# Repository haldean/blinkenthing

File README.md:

blinkenthing
============

turning a black bike into a rainbow monstrosity

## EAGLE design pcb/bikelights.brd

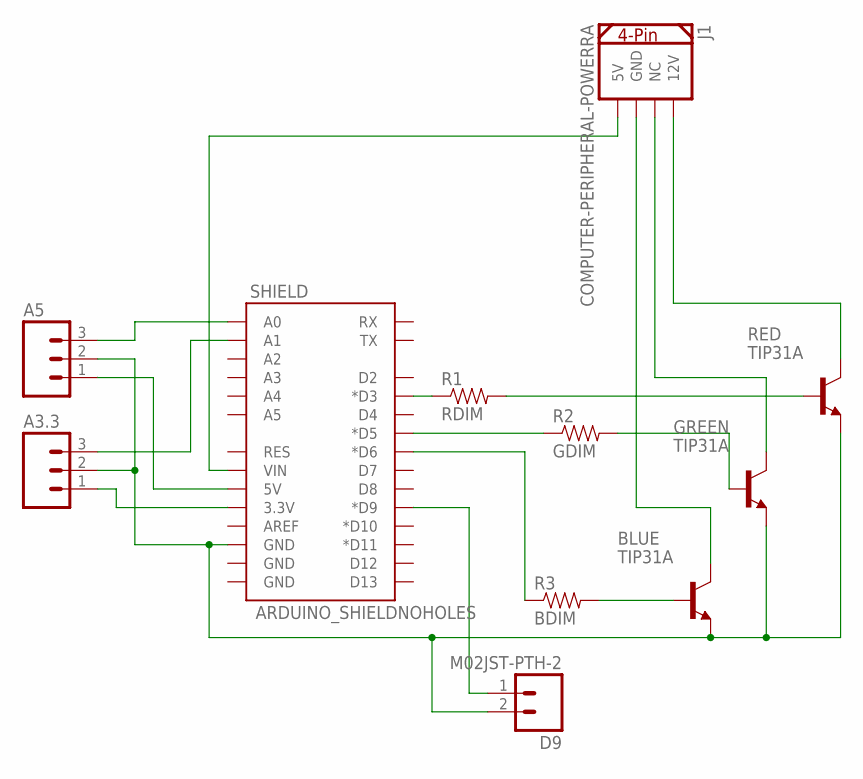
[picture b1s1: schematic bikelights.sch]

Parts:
A3.3, A5: M03JST-PTH; JST-3-PTH
BLUE: TIP31A; TO220
D9: M02JST-PTH-2; JST-2-PTH
GREEN: TIP31A; TO220
J1: COMPUTER-PERIPHERAL-POWERRA; COMPUTER-PERIPHERAL-POWER-RA
R1: RDIM; AXIAL-0.3EZ
R2: GDIM; AXIAL-0.3EZ
R3: BDIM; AXIAL-0.3EZ
RED: TIP31A; TO220
SHIELD: ARDUINO_SHIELDNOHOLES; DUEMILANOVE_SHIELD_NOHOLES

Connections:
unnamed: R1.P$1 (1), SHIELD.D3 (*D3)
unnamed: GREEN.1 (B), R2.P$2 (2)
unnamed: BLUE.1 (B), R3.P$2 (2)
unnamed: A3.3.2, A5.2, BLUE.3 (E), D9.2, GREEN.3 (E), RED.3 (E), SHIELD.GND@2 (GND)
unnamed: BLUE.2 (C), J1.GND
unnamed: GREEN.2 (C), J1.NC
unnamed: J1.12V, RED.2 (C)
unnamed: J1.5V, SHIELD.VIN
unnamed: R2.P$1 (1), SHIELD.D5 (*D5)
unnamed: R3.P$1 (1), SHIELD.D6 (*D6)
unnamed: R1.P$2 (2), RED.1 (B)
unnamed: A5.1, SHIELD.5V
unnamed: D9.1, SHIELD.D9 (*D9)
unnamed: A5.3, SHIELD.A0
unnamed: A3.3.3, SHIELD.A1
unnamed: A3.3.1, SHIELD.3.3V

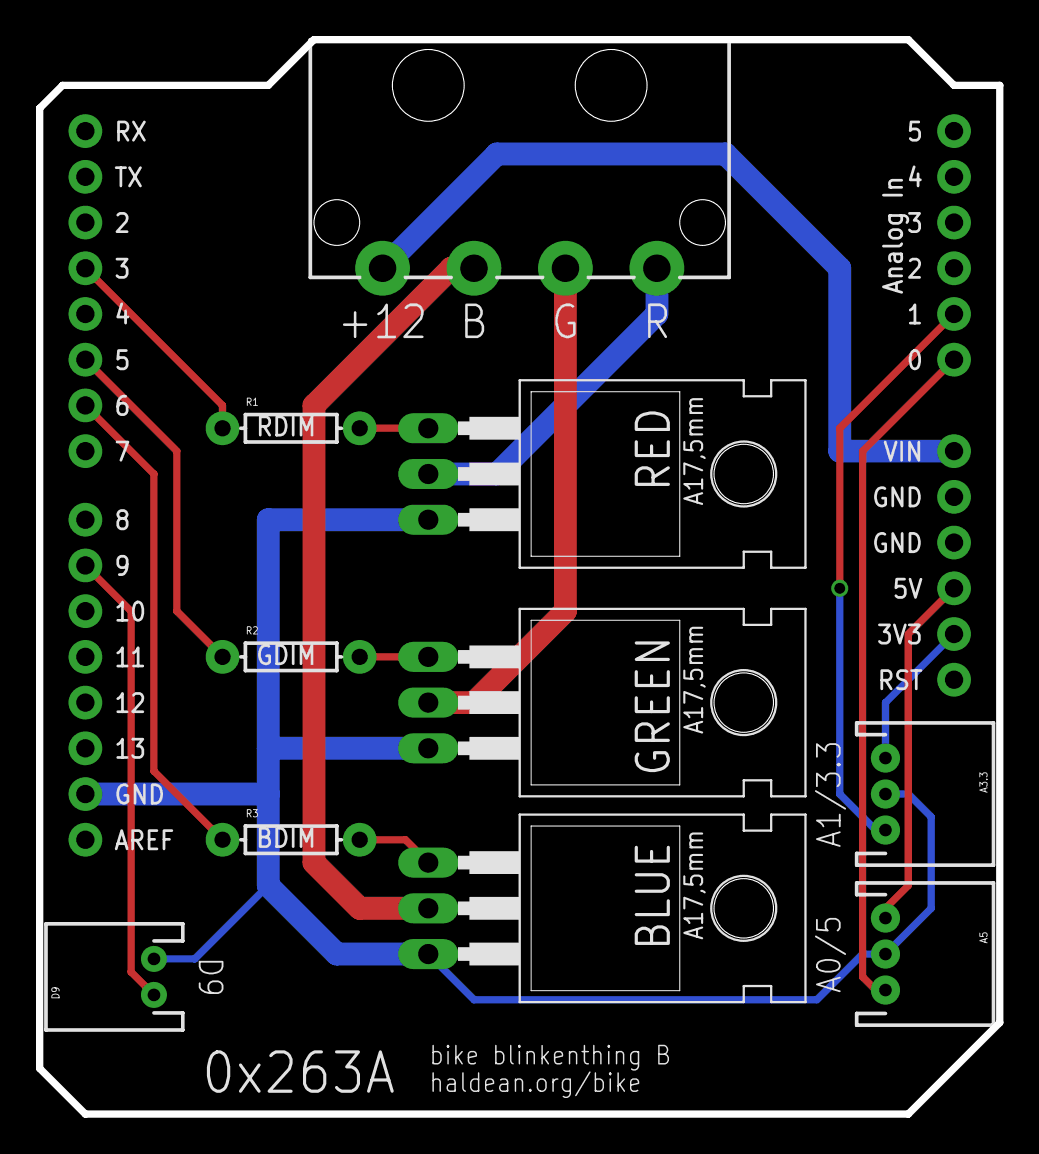
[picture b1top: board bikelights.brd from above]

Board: 2 copper layers, 53.3 x 59.7 mm, 11 parts (0 on the bottom side), 16 nets.

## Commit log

2014-05-13 PCBv0 and arduino sketch
2014-06-07 New PCB for blinkenthing B.

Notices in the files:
parts and their libraries:
SparkFun-Boards: Licensing: Creative Commons ShareAlike 4.0 International - https://creativecommons.org/licenses/by-sa/4.0
